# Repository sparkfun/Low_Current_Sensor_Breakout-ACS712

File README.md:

**NOTE:** *This product has been retired from our catalog. There is an updated drop-in replacement with the ACS723 available: [SEN-14544](https://github.com/sparkfun/Current_Sensor_Breakout-ACS723-Low_Current). If you are looking for more up-to-date info, please check out some of these resources to see how other users are still hacking and improving on this product version.*

* *[SparkFun Forum](https://forum.sparkfun.com/)*
* *[Comments Here on GitHub](https://github.com/sparkfun/Low_Current_Sensor_Breakout-ACS712/issues)*
* *[IRC Channel](https://www.sparkfun.com/news/263)*

SparkFun Low Current Sensor Breakout Board - ACS712
======================================================

[*SparkFun Low Current Sensor Breakout Board - ACS712 (SEN-08883)*](https://www.sparkfun.com/products/8883) 

This current sensor gives precise current measurement for both AC and DC signals. 
These are good sensors for metering and measuring overall power consumption of systems.
The ACS712 Low Current Sensor Breakout outputs an analog voltage that varies linearly with sensed current.

Repository Contents
-------------------
* **/Hardware** - All Eagle design files (.brd, .sch)

Documentation
--------------
* **[Hookup Guide](https://learn.sparkfun.com/tutorials/acs712-low-current-sensor-hookup-guide)** - Basic hookup guide for the ACS712.

Product Versions
----------------

* [SEN-08883 (RETIRED)](https://www.sparkfun.com/products/8883)- Initial release; ACS712 Version of this Board

License Information
-------------------

This product is _**open source**_! 

Please review the LICENSE.md file for license information. 

If you have any questions or concerns on licensing, please contact techsupport@sparkfun.com.

Distributed as-is; no warranty is given.

- Your friends at SparkFun.

_<COLLABORATION CREDIT>_

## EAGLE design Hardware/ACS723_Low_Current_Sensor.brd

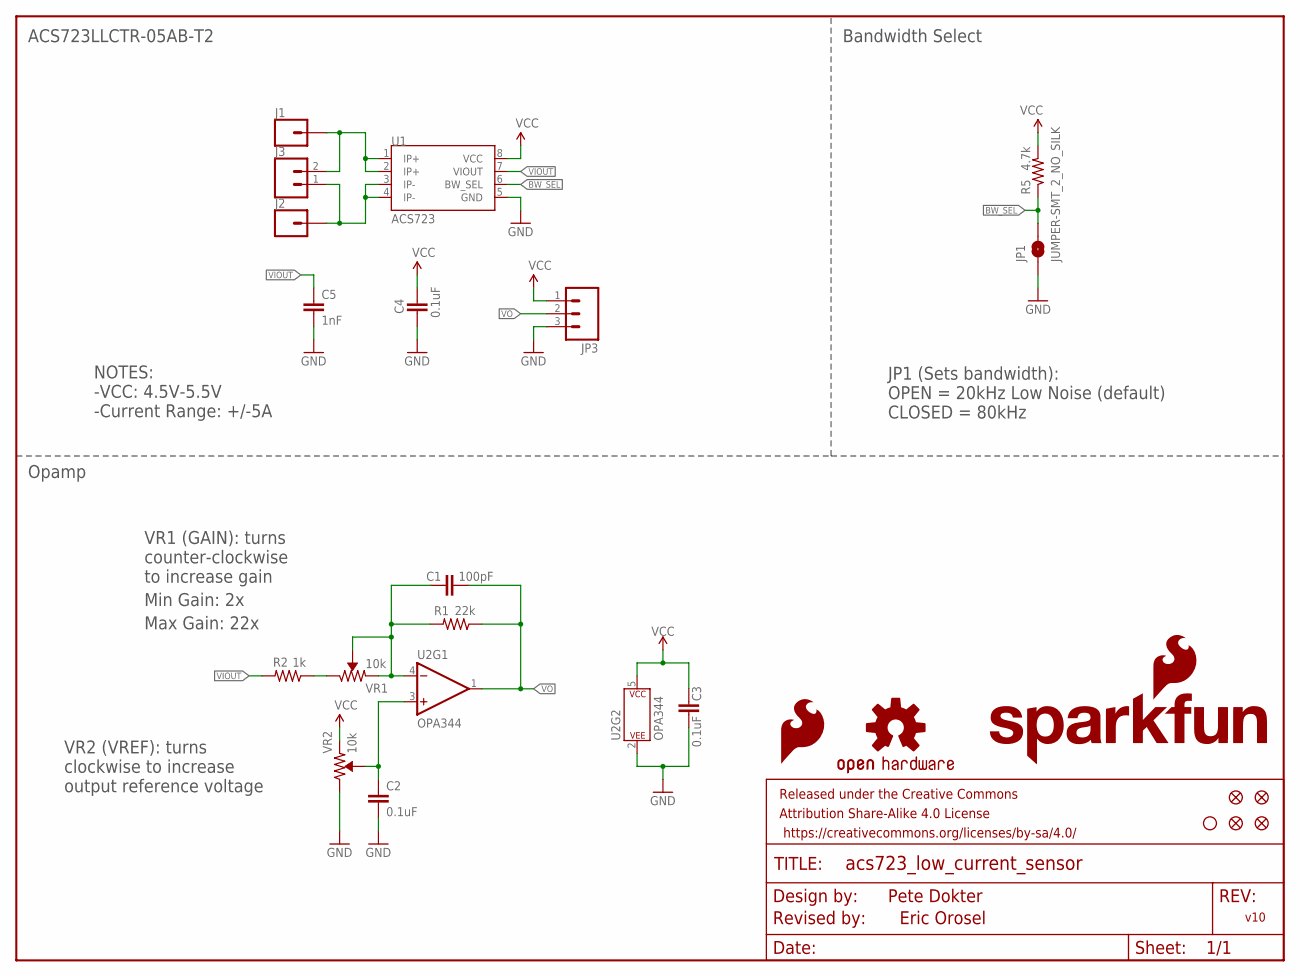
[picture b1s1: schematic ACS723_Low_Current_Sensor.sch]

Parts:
C1: 100pF; 0603
C2, C3, C4: 0.1uF; 0603
C5: 1nF; 0603
FD1, FD2, FD3, FD4: FIDUCIAL1X2; FIDUCIAL-1X2
FRAME1: FRAME-LETTER; CREATIVE_COMMONS
H1: STAND-OFFTIGHT; STAND-OFF-TIGHT
J1, J2: CONN_01SMTSO-256-ET-0.165DIA; SMTSO-256-ET-0.165DIA
J3: CONN_021X02_NO_SILK; 1X02_NO_SILK
JP1: JUMPER-SMT_2_NO_SILK; SMT-JUMPER_2_NO_SILK
JP3: M03PTH; 1X03
LOGO1: SFE_LOGO_NAME_FLAME.1_INCH; SFE_LOGO_NAME_FLAME_.1
LOGO2: OSHW-LOGOS; OSHW-LOGO-S
LOGO3: SFE_LOGO_FLAME.1_INCH; SFE_LOGO_FLAME_.1
R1: 22k; 0603
R2: 1k; 0603
R5: 4.7k; 0603
U1: ACS723; SO08
U2: OPA344; SOT23-5
VR1, VR2: 10k; TRIMPOT-SMD-TC33X

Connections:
5V: C3.1, C4.2, JP3.1, R5.2, U1.8 (VCC), U2.5 (P$V+), VR2.3 (CCW)
BW_SEL: JP1.2, R5.1, U1.6 (BW_SEL)
GND: C2.2, C3.2, C4.1, C5.2, JP1.1, JP3.3, U1.5 (GND), U2.2 (P$V-), VR2.1 (CW)
IP+: J1.P$1, J3.2, U1.1 (IP+), U1.2 (IP+)
IP-: J2.P$1, J3.1, U1.3 (IP-), U1.4 (IP-)
unnamed: R2.1, VR1.1 (CW)
unnamed: C1.2, R1.2, U2.4 (-IN), VR1.2 (WIPER), VR1.3 (CCW)
unnamed: C2.1, U2.3 (+IN), VR2.2 (WIPER)
VIOUT: C5.1, R2.2, U1.7 (VIOUT)
VO: C1.1, JP3.2, R1.1, U2.1 (OUT)

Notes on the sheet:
v10
Pete Dokter
Revised by:
Eric Orosel
Opamp
JP1 (Sets bandwidth):
CLOSED = 80kHz
OPEN = 20kHz Low Noise (default)
Bandwidth Select
VR1 (GAIN): turns counter-clockwise to increase gain
VR2 (VREF): turns clockwise to increase output reference voltage
ACS723LLCTR-05AB-T2
-Current Range: +/-5A
-VCC: 4.5V-5.5V
NOTES:
Max Gain: 22x
Min Gain: 2x

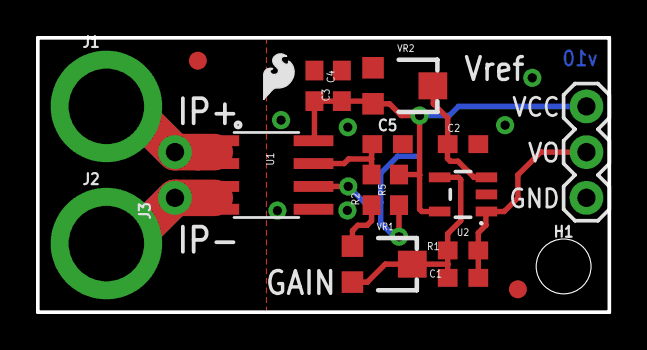
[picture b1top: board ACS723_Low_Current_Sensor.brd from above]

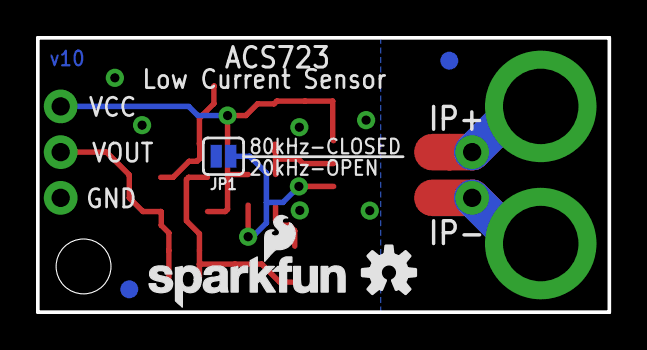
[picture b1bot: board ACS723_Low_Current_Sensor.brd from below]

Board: 2 copper layers, 31.8 x 15.2 mm, 26 parts (5 on the bottom side), 10 nets.

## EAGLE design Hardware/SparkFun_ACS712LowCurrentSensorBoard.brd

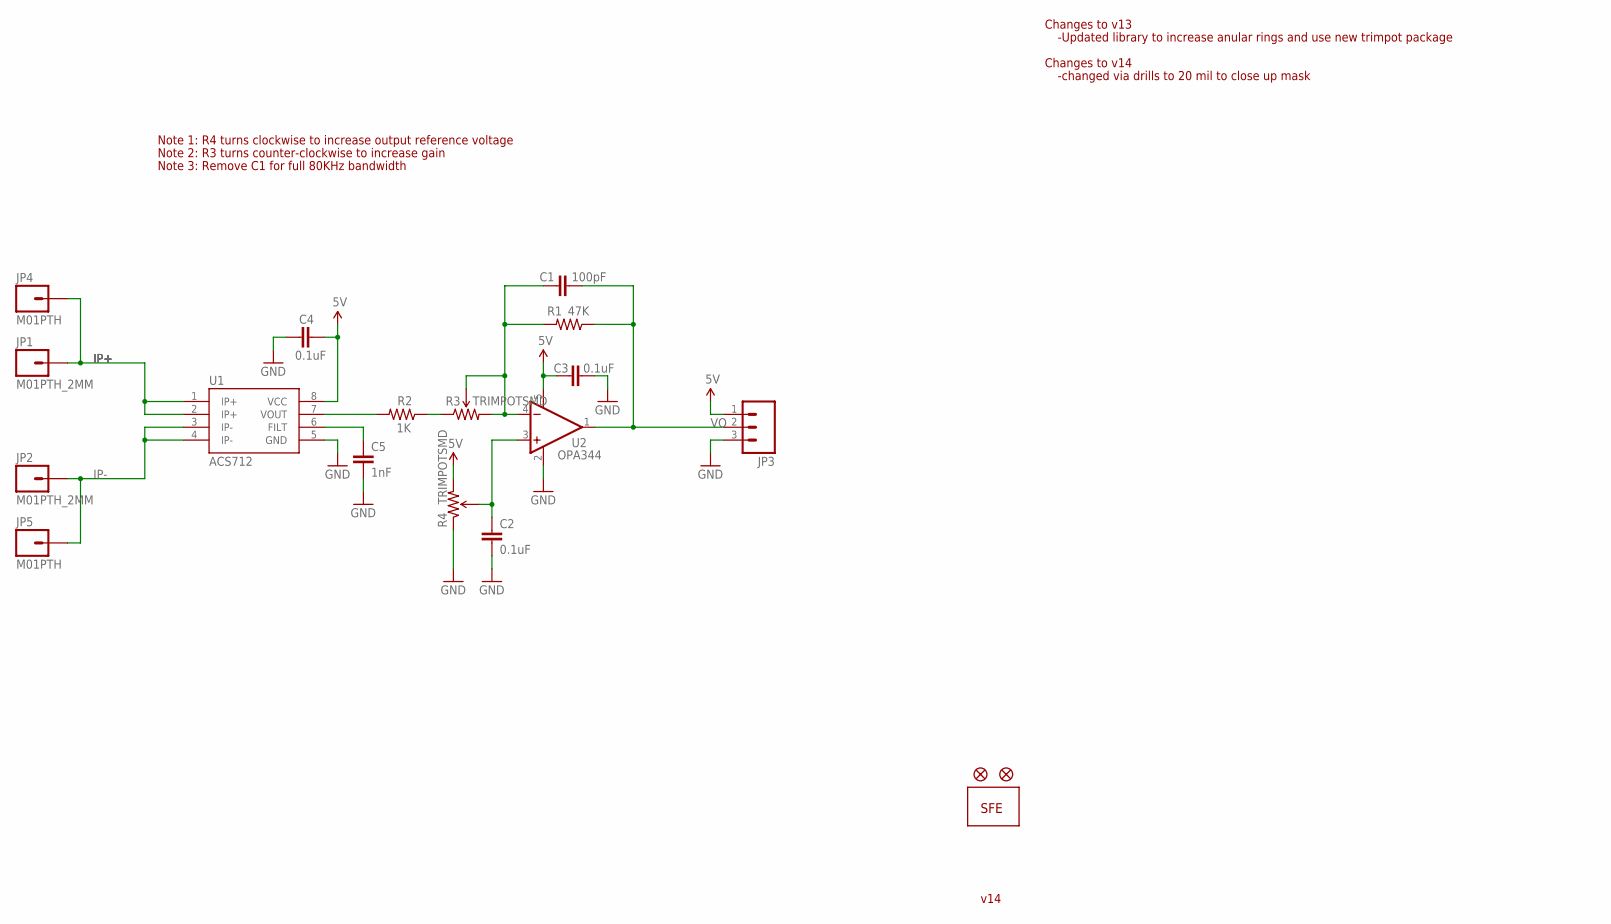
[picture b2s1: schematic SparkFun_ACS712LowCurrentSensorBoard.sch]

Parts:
C1: 100pF; 0402-CAP
C2, C3, C4: 0.1uF; 0402-CAP
C5: 1nF; 0402-CAP
JP1, JP2: M01PTH_2MM; 1X01_2MM
JP3: M03PTH; 1X03
JP4, JP5: M01PTH; 1X01
R1: 47K; 0402-RES
R2: 1K; 0402-RES
R3, R4: TRIMPOTSMD; TRIMPOT-3MM
U1: ACS712; SO08
U2: OPA344; SOT23-5
U$1, U$3: FIDUCIALUFIDUCIAL; MICRO-FIDUCIAL
U$2: LOGO-SFENEW; SFE-NEW-WEBLOGO

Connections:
5V: C3.1, C4.2, JP3.1, R4.3 (CW), U1.8 (VCC), U2.5 (V+)
GND: C2.2, C3.2, C4.1, C5.2, JP3.3, R4.1 (CCW), U1.5 (GND), U2.2 (V-)
IP+: JP1.1, JP4.1, U1.1 (IP+), U1.2 (IP+)
IP-: JP2.1, JP5.1, U1.3 (IP-), U1.4 (IP-)
unnamed: R2.2, U1.7 (VOUT)
unnamed: R2.1, R3.1 (CCW)
unnamed: C1.2, R1.2, R3.2 (WIPER), R3.3 (CW), U2.4 (-IN)
unnamed: C2.1, R4.2 (WIPER), U2.3 (+IN)
unnamed: C5.1, U1.6 (FILT)
VO: C1.1, JP3.2, R1.1, U2.1 (OUT)

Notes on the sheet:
Note 1: R4 turns clockwise to increase output reference voltage
Note 2: R3 turns counter-clockwise to increase gain
Note 3: Remove C1 for full 80KHz bandwidth
Changes to v13
-Updated library to increase anular rings and use new trimpot package
Changes to v14
-changed via drills to 20 mil to close up mask
v14

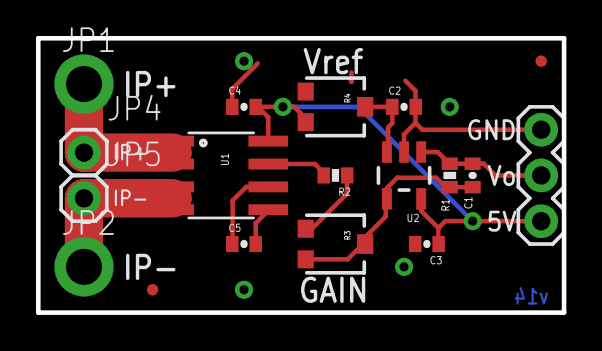
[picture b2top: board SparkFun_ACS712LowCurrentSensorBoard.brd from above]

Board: 2 copper layers, 29.2 x 15.2 mm, 19 parts (1 on the bottom side), 10 nets.

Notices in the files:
parts and their libraries:
SparkFun-Capacitors: Licensing: Creative Commons ShareAlike 4.0 International - https://creativecommons.org/licenses/by-sa/4.0
SparkFun-Aesthetics: Released under the Creative Commons Attribution Share-Alike 4.0 License
SparkFun-Aesthetics: https://creativecommons.org/licenses/by-sa/4.0
